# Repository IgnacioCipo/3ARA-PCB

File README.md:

# 3ARA-PCB

# Introduction
This repo holds the electronic boards of the project designed using KiCad.

# Images

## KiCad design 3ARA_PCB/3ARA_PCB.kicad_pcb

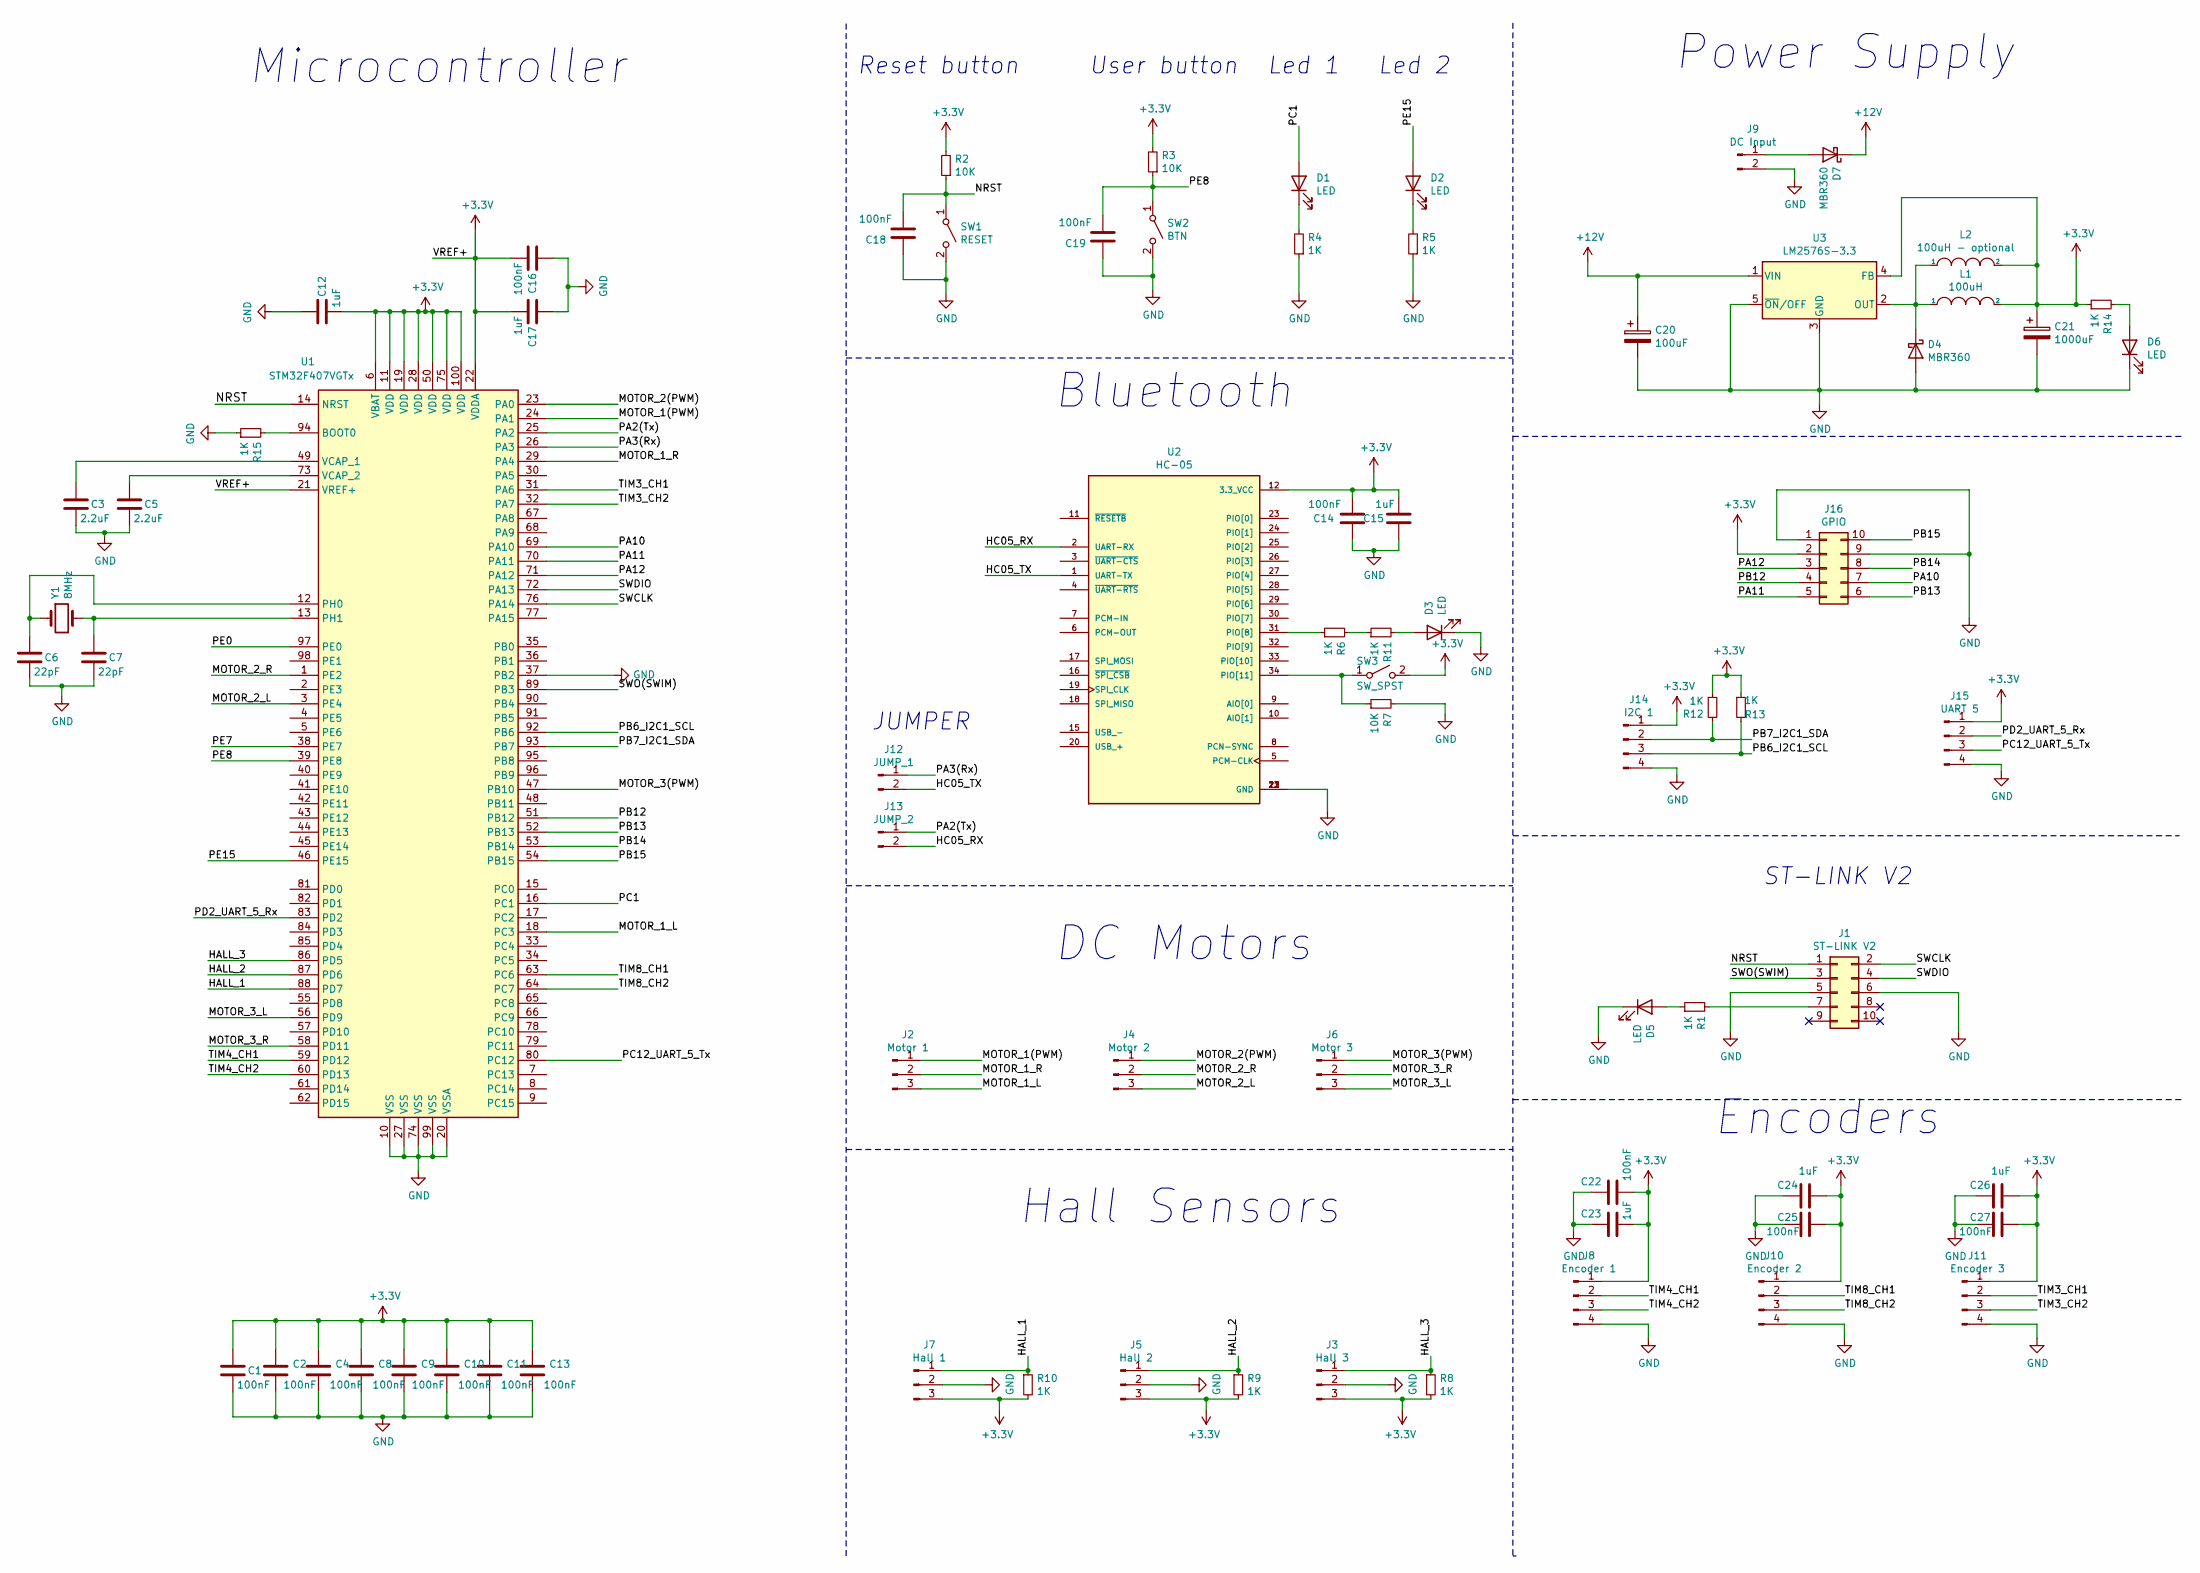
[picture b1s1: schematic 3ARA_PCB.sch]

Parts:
C1, C2, C4, C8, C9, C10, C11, C13, C14, C16, C18, C19, C22, C25, C27: 100nF; C_0805_2012Metric_Pad1.18x1.45mm_HandSolder
C3, C5: 2.2uF; C_Disc_D3.8mm_W2.6mm_P2.50mm
C6, C7: 22pF; C_0805_2012Metric_Pad1.18x1.45mm_HandSolder
C12, C15, C17, C23, C24, C26: 1uF; C_0805_2012Metric_Pad1.18x1.45mm_HandSolder
C20: 100uF; CP_Elec_6.3x5.4
C21: 1000uF; CP_Radial_D8.0mm_P3.50mm
D1, D6: LED; LED_1206_3216Metric_Pad1.42x1.75mm_HandSolder
D2, D3, D5: LED; LED_0805_2012Metric_Pad1.15x1.40mm_HandSolder
D4, D7: MBR360; D_SMA_Handsoldering
J1: ST-LINK V2; IDC-Header_2x05_P2.54mm_Vertical
J2: Motor 1; JST_EH_B3B-EH-A_1x03_P2.50mm_Vertical
J3: Hall 3; JST_EH_B3B-EH-A_1x03_P2.50mm_Vertical
J4: Motor 2; JST_EH_B3B-EH-A_1x03_P2.50mm_Vertical
J5: Hall 2; JST_EH_B3B-EH-A_1x03_P2.50mm_Vertical
J6: Motor 3; JST_EH_B3B-EH-A_1x03_P2.50mm_Vertical
J7: Hall 1; JST_EH_B3B-EH-A_1x03_P2.50mm_Vertical
J8: Encoder 1; JST_EH_B4B-EH-A_1x04_P2.50mm_Vertical
J9: DC Input; JST_EH_B2B-EH-A_1x02_P2.50mm_Vertical
J10: Encoder 2; JST_EH_B4B-EH-A_1x04_P2.50mm_Vertical
J11: Encoder 3; JST_EH_B4B-EH-A_1x04_P2.50mm_Vertical
J12: JUMP_1; PinHeader_1x02_P2.54mm_Vertical
J13: JUMP_2; PinHeader_1x02_P2.54mm_Vertical
J14: I2C 1; JST_EH_B4B-EH-A_1x04_P2.50mm_Vertical
J15: UART 5; JST_EH_B4B-EH-A_1x04_P2.50mm_Vertical
J16: GPIO; PinHeader_2x05_P2.54mm_Vertical
L1: 100uH; L_12x12mm_H6mm
L2: 100uH - optional; L_Axial_L9.5mm_D4.0mm_P15.24mm_Horizontal_Fastron_SMCC
R1, R4, R5, R6, R8, R9, R10, R11, R12, R13, R14, R15: 1K; R_0805_2012Metric_Pad1.20x1.40mm_HandSolder
R2, R3, R7: 10K; R_0805_2012Metric_Pad1.20x1.40mm_HandSolder
SW1: RESET; SW_PUSH_6mm
SW2: BTN; SW_PUSH_6mm
SW3: SW_SPST; SW_PUSH_6mm
U1: STM32F407VGTx; LQFP-100_14x14mm_P0.5mm
U2: HC-05; XCVR_HC-05; PARTREV v1.0
U3: LM2576S-3.3; TO-263-5_TabPin3
Y1: 8MHz; Crystal_HC49-U_Vertical

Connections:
+3V3: C1.1, C2.1, C4.1, C8.1, C9.1, C10.1, C11.1, C12.2, C13.1, C14.2, C15.2, C16.2, C17.2, C21.1, C22.2, C23.2, C24.1, C25.1, C26.1, C27.1, J3.3, J5.3, J7.3, J8.1, J10.1, J11.1, J14.1, J15.1, J16.2, L1.2, L2.2, R2.2, R3.2, R8.2, R9.2, R10.2, R12.1, R13.1, R14.1, SW3.2 (B), U1.6 (VBAT), U1.11 (VDD), U1.19 (VDD), U1.21 (VREF+), U1.22 (VDDA), U1.28 (VDD), U1.50 (VDD), U1.75 (VDD), U1.100 (VDD), U2.12 (3.3_VCC), U3.4 (FB)
+12V: C20.1, D7.1 (K), U3.1 (VIN)
/HALL_1: J7.1, R10.1, U1.88 (PD7)
/HALL_2: J5.1, R9.1, U1.87 (PD6)
/HALL_3: J3.1, R8.1, U1.86 (PD5)
/HC05_RX: J13.2, U2.2 (UART-RX)
/HC05_TX: J12.2, U2.1 (UART-TX)
/MOTOR_1(PWM): J2.1, U1.24 (PA1)
/MOTOR_1_L: J2.3, U1.18 (PC3)
/MOTOR_1_R: J2.2, U1.29 (PA4)
/MOTOR_2(PWM): J4.1, U1.23 (PA0)
/MOTOR_2_L: J4.3, U1.3 (PE4)
/MOTOR_2_R: J4.2, U1.1 (PE2)
/MOTOR_3(PWM): J6.1, U1.47 (PB10)
/MOTOR_3_L: J6.3, U1.56 (PD9)
/MOTOR_3_R: J6.2, U1.58 (PD11)
/NRST: C18.2, J1.1, R2.1, SW1.1 (A), U1.14 (NRST)
/PA2(Tx): J13.1, U1.25 (PA2)
/PA3(Rx): J12.1, U1.26 (PA3)
/PA10: J16.7, U1.69 (PA10)
/PA11: J16.5, U1.70 (PA11)
/PA12: J16.3, U1.71 (PA12)
/PB6_I2C1_SCL: J14.3, R13.2, U1.92 (PB6)
/PB7_I2C1_SDA: J14.2, R12.2, U1.93 (PB7)
/PB12: J16.4, U1.51 (PB12)
/PB13: J16.6, U1.52 (PB13)
/PB14: J16.8, U1.53 (PB14)
/PB15: J16.10, U1.54 (PB15)
/PC1: D1.2 (A), U1.16 (PC1)
/PC12_UART_5_Tx: J15.3, U1.80 (PC12)
/PD2_UART_5_Rx: J15.2, U1.83 (PD2)
/PE8: C19.2, R3.1, SW2.1 (A), U1.39 (PE8)
/PE15: D2.2 (A), U1.46 (PE15)
/SWCLK: J1.2, U1.76 (PA14)
/SWDIO: J1.4, U1.72 (PA13)
/SWO(SWIM): J1.3, U1.89 (PB3)
/TIM3_CH1: J11.2, U1.31 (PA6)
/TIM3_CH2: J11.3, U1.32 (PA7)
/TIM4_CH1: J8.2, U1.59 (PD12)
/TIM4_CH2: J8.3, U1.60 (PD13)
/TIM8_CH1: J10.2, U1.63 (PC6)
/TIM8_CH2: J10.3, U1.64 (PC7)
GND: C1.2, C2.2, C3.2, C4.2, C5.2, C6.2, C7.2, C8.2, C9.2, C10.2, C11.2, C12.1, C13.2, C14.1, C15.1, C16.1, C17.1, C18.1, C19.1, C20.2, C21.2, C22.1, C23.1, C24.2, C25.2, C26.2, C27.2, D3.1 (K), D4.2 (A), D5.1 (K), D6.1 (K), J1.5, J1.6, J3.2, J5.2, J7.2, J8.4, J9.2, J10.4, J11.4, J14.4, J15.4, J16.1, J16.9, R4.1, R5.1, R7.2, R15.1, SW1.2 (B), SW2.2 (B), U1.10 (VSS), U1.20 (VSSA), U1.27 (VSS), U1.37 (PB2), U1.74 (VSS), U1.99 (VSS), U2.13 (GND), U2.21 (GND), U2.22 (GND), U3.3 (GND), U3.5 (~ON~/OFF)
unnamed: C3.1, U1.49 (VCAP_1)
unnamed: C5.1, U1.73 (VCAP_2)
unnamed: C6.1, U1.12 (PH0), Y1.1
unnamed: C7.1, U1.13 (PH1), Y1.2
unnamed: D1.1 (K), R4.2
unnamed: D2.1 (K), R5.2
unnamed: D3.2 (A), R11.2
unnamed: D4.1 (K), L1.1, L2.1, U3.2 (OUT)
unnamed: D5.2 (A), R1.1
unnamed: D6.2 (A), R14.2
unnamed: D7.2 (A), J9.1
unnamed: J1.7, R1.2
unnamed: R6.1, U2.31 (PIO[8])
unnamed: R7.1, SW3.1 (A), U2.34 (PIO[11])
unnamed: R6.2, R11.1
unnamed: R15.2, U1.94 (BOOT0)

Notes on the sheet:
Microcontroller
Reset button
Led 1
Led 2
User button
ST-LINK V2
Bluetooth
DC Motors
Hall Sensors
Encoders
Power Supply
JUMPER

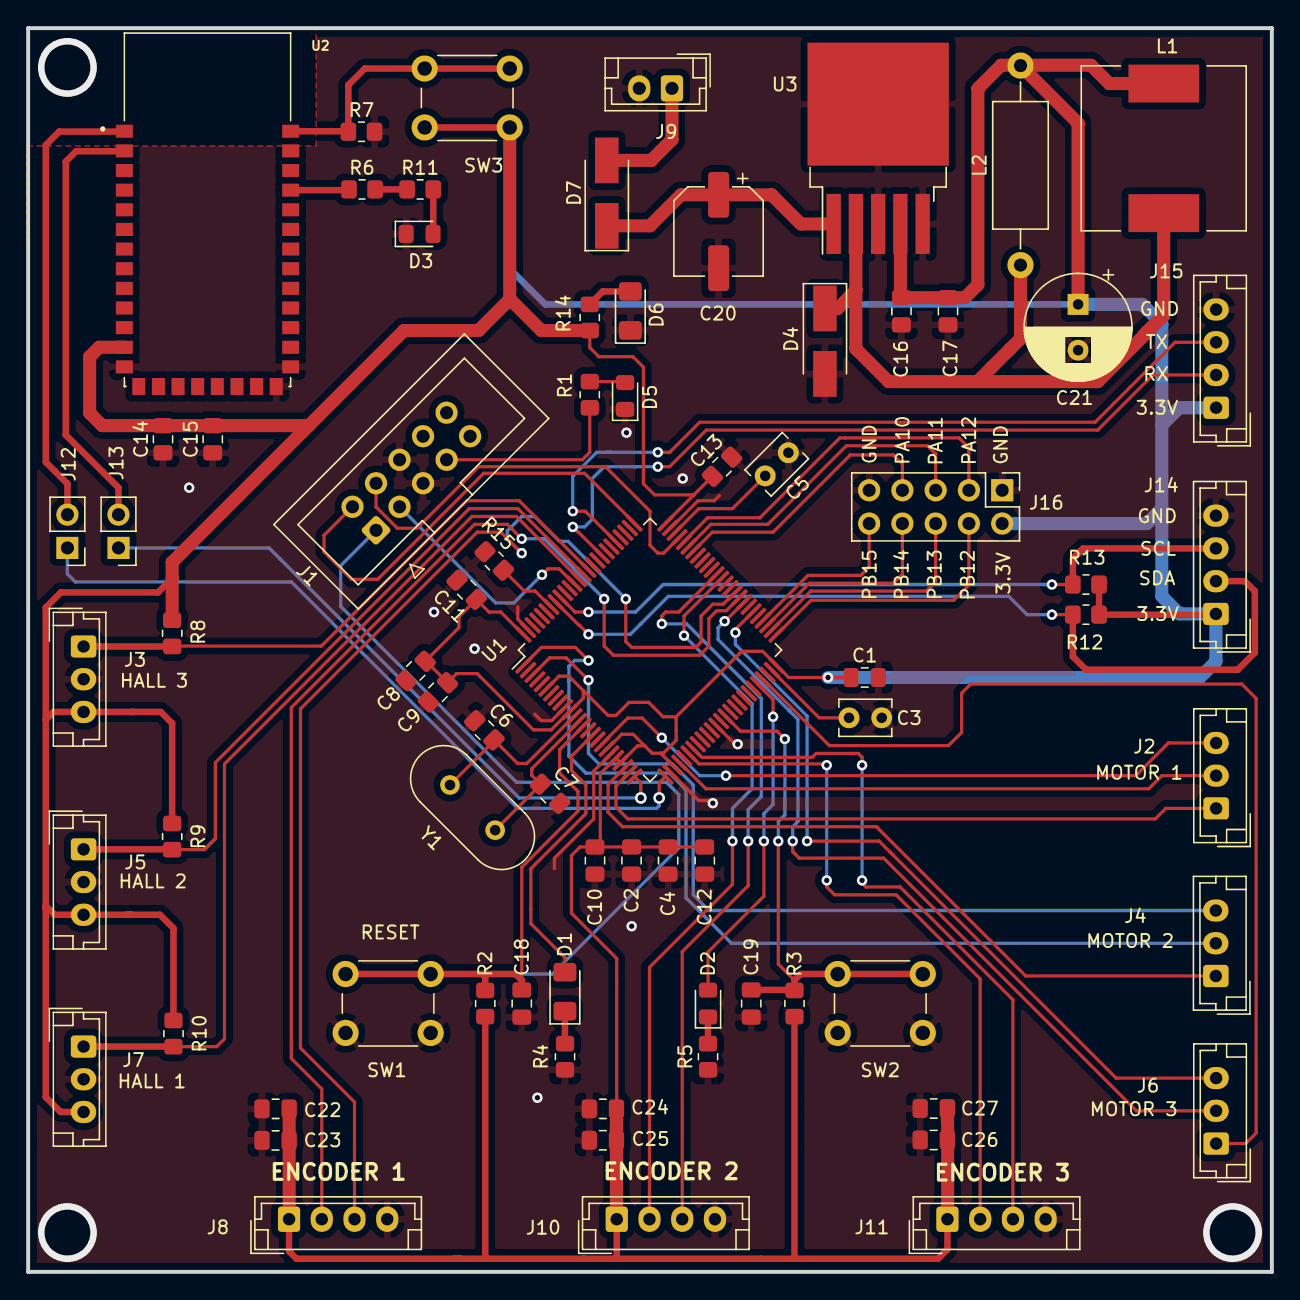
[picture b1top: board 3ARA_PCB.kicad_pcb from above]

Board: 2 copper layers, 95.0 x 95.0 mm, 74 parts (0 on the bottom side), 59 nets.

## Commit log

2021-09-02 Project creation and schematic started
2021-09-15 Continuacion del esquematico
2021-09-24 Avance con el PCB
2021-09-27 Agregado de gpios a pines
2021-09-30 Generación de la BOM
2021-09-30 Agregado de R pull down a boot 0 y capacitores en alimentacion
2021-11-12 Agregado de diseño 3D para HC05
2021-11-12 Agregado de diseño 3D para inductor SMD 100uH
